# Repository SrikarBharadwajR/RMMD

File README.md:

# Project RMMD
RoboManipal Motor Driver
An Open Souce DC Brushed Motor Driver

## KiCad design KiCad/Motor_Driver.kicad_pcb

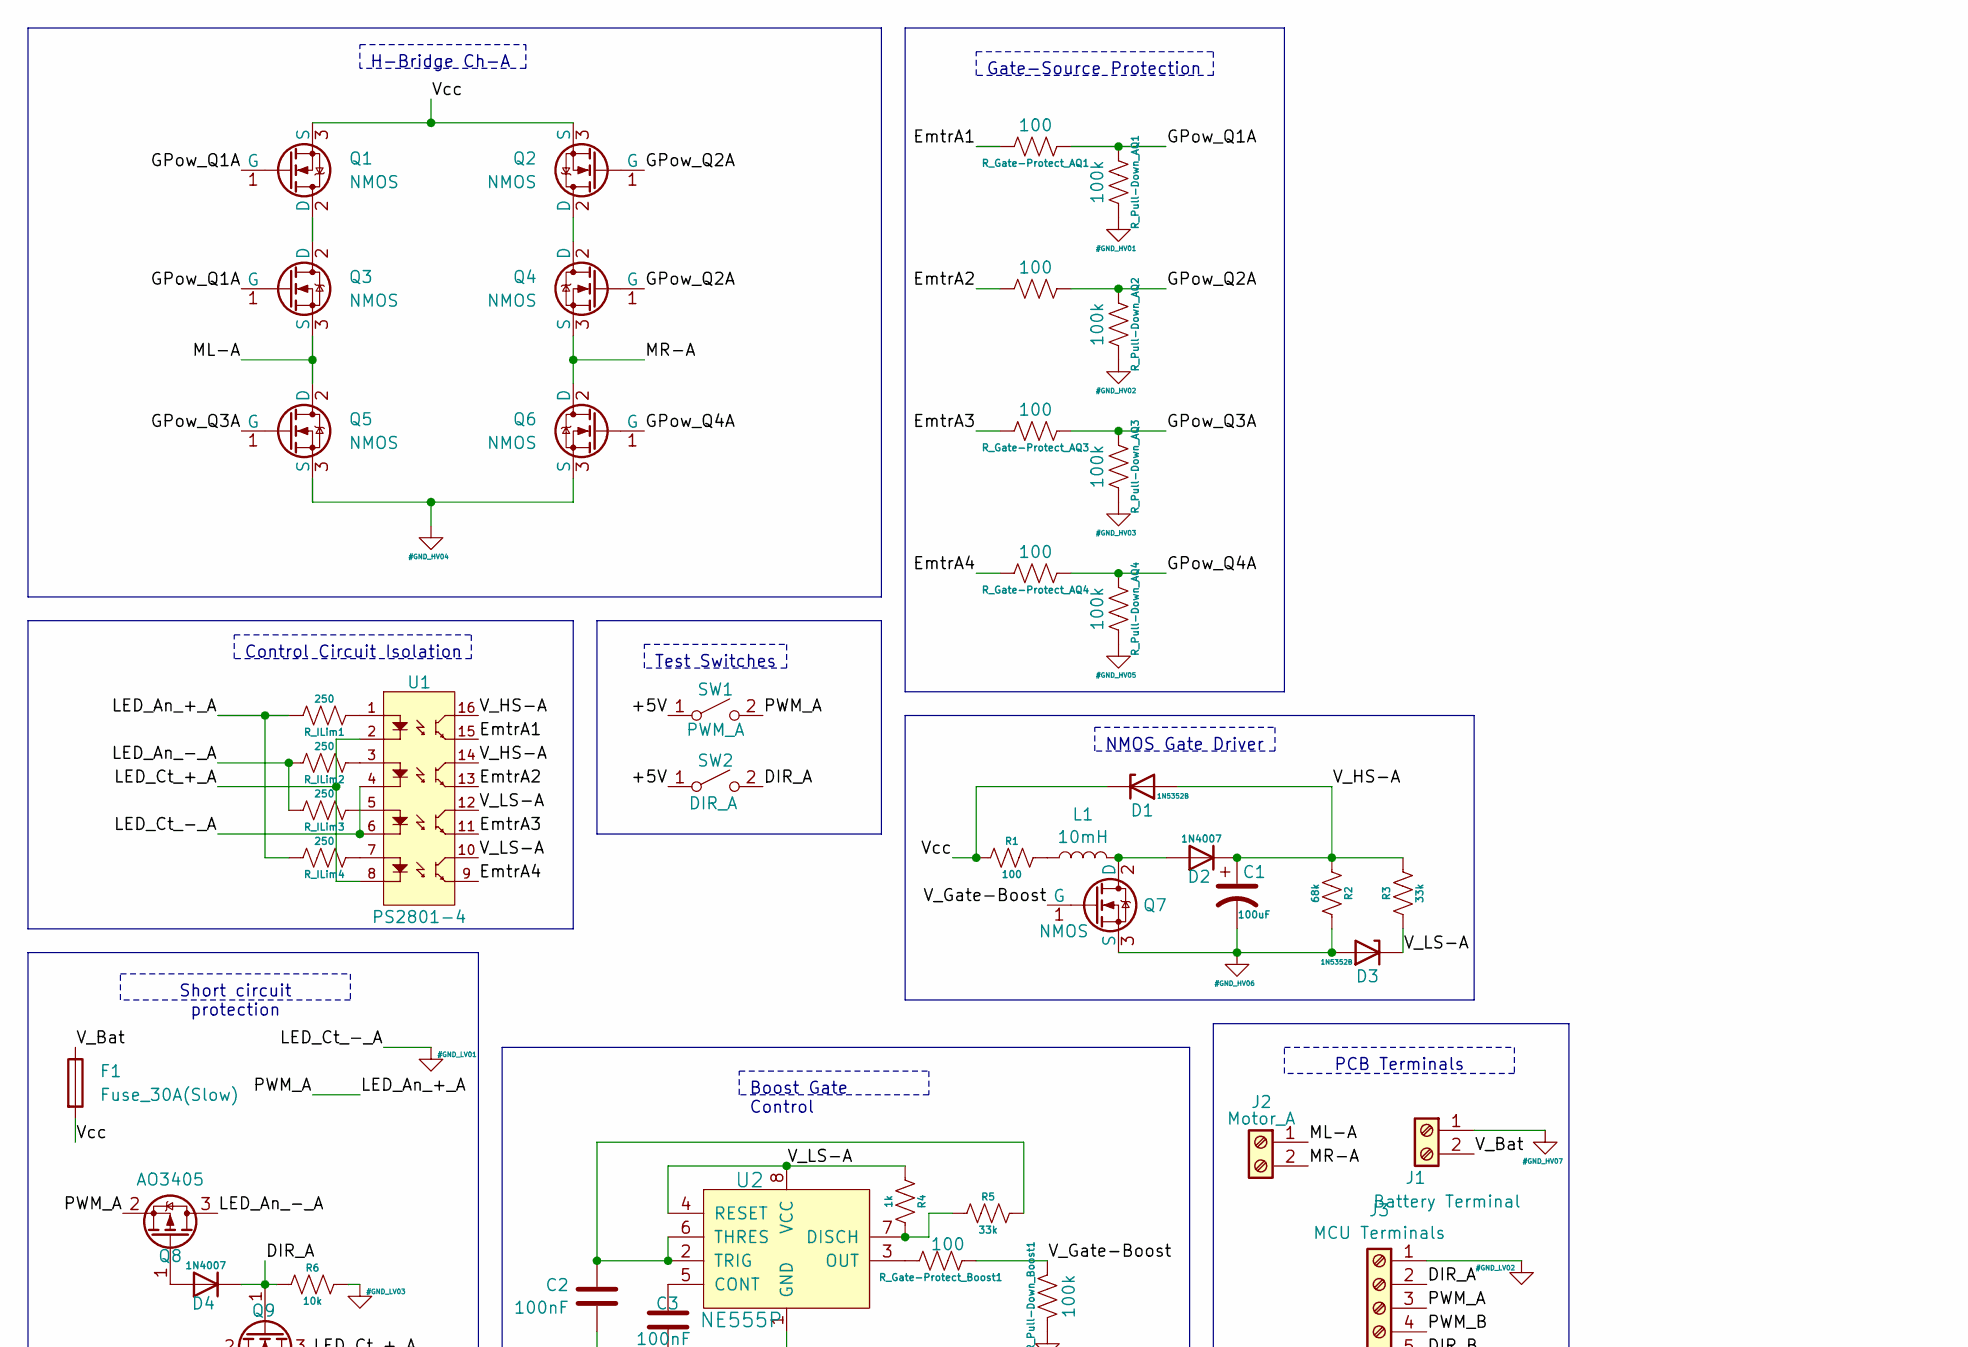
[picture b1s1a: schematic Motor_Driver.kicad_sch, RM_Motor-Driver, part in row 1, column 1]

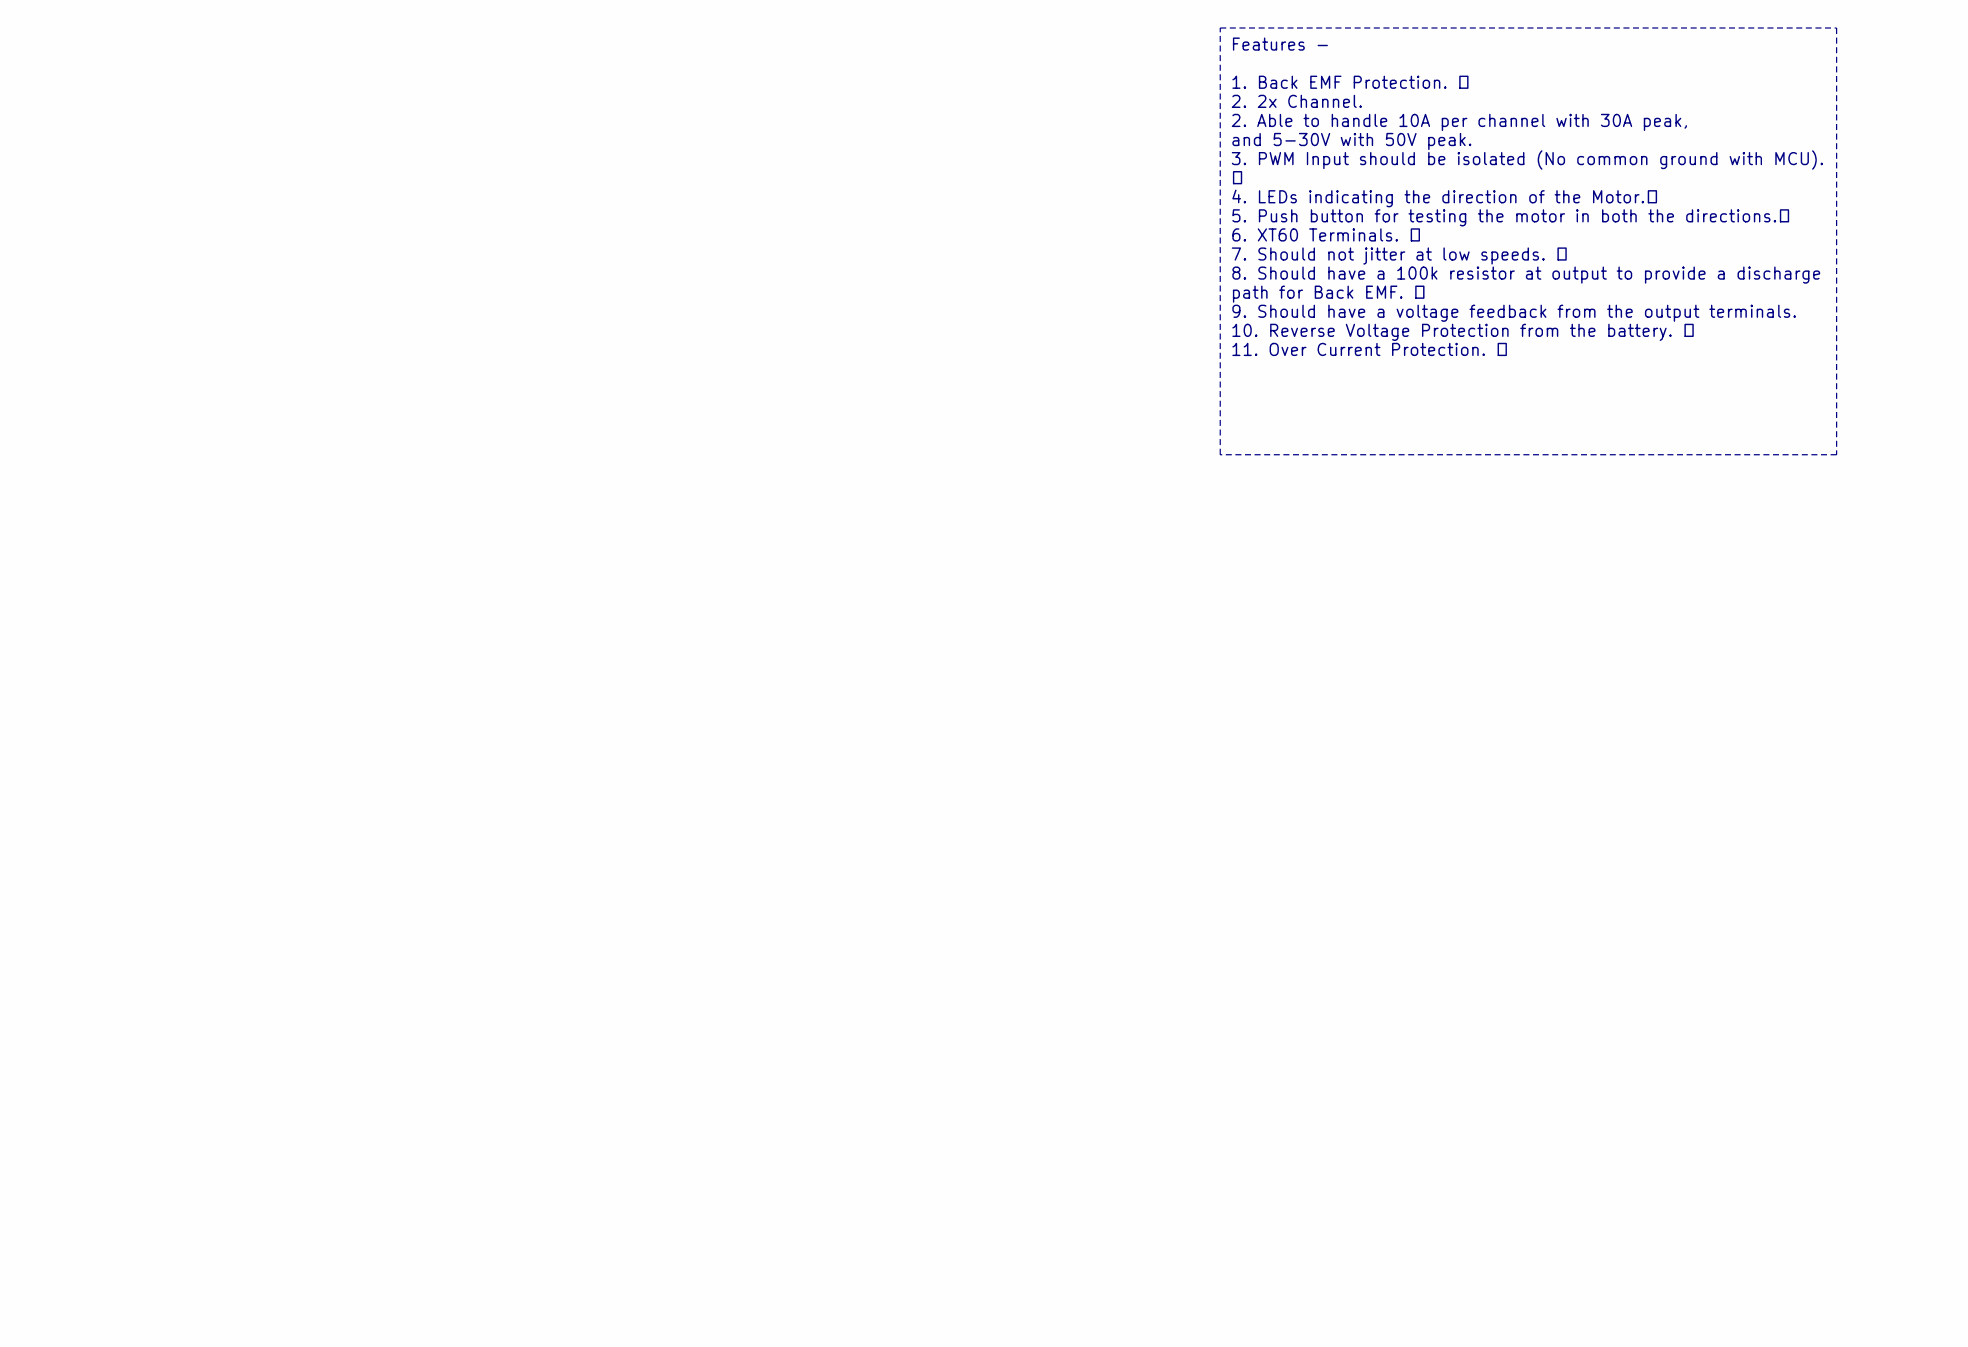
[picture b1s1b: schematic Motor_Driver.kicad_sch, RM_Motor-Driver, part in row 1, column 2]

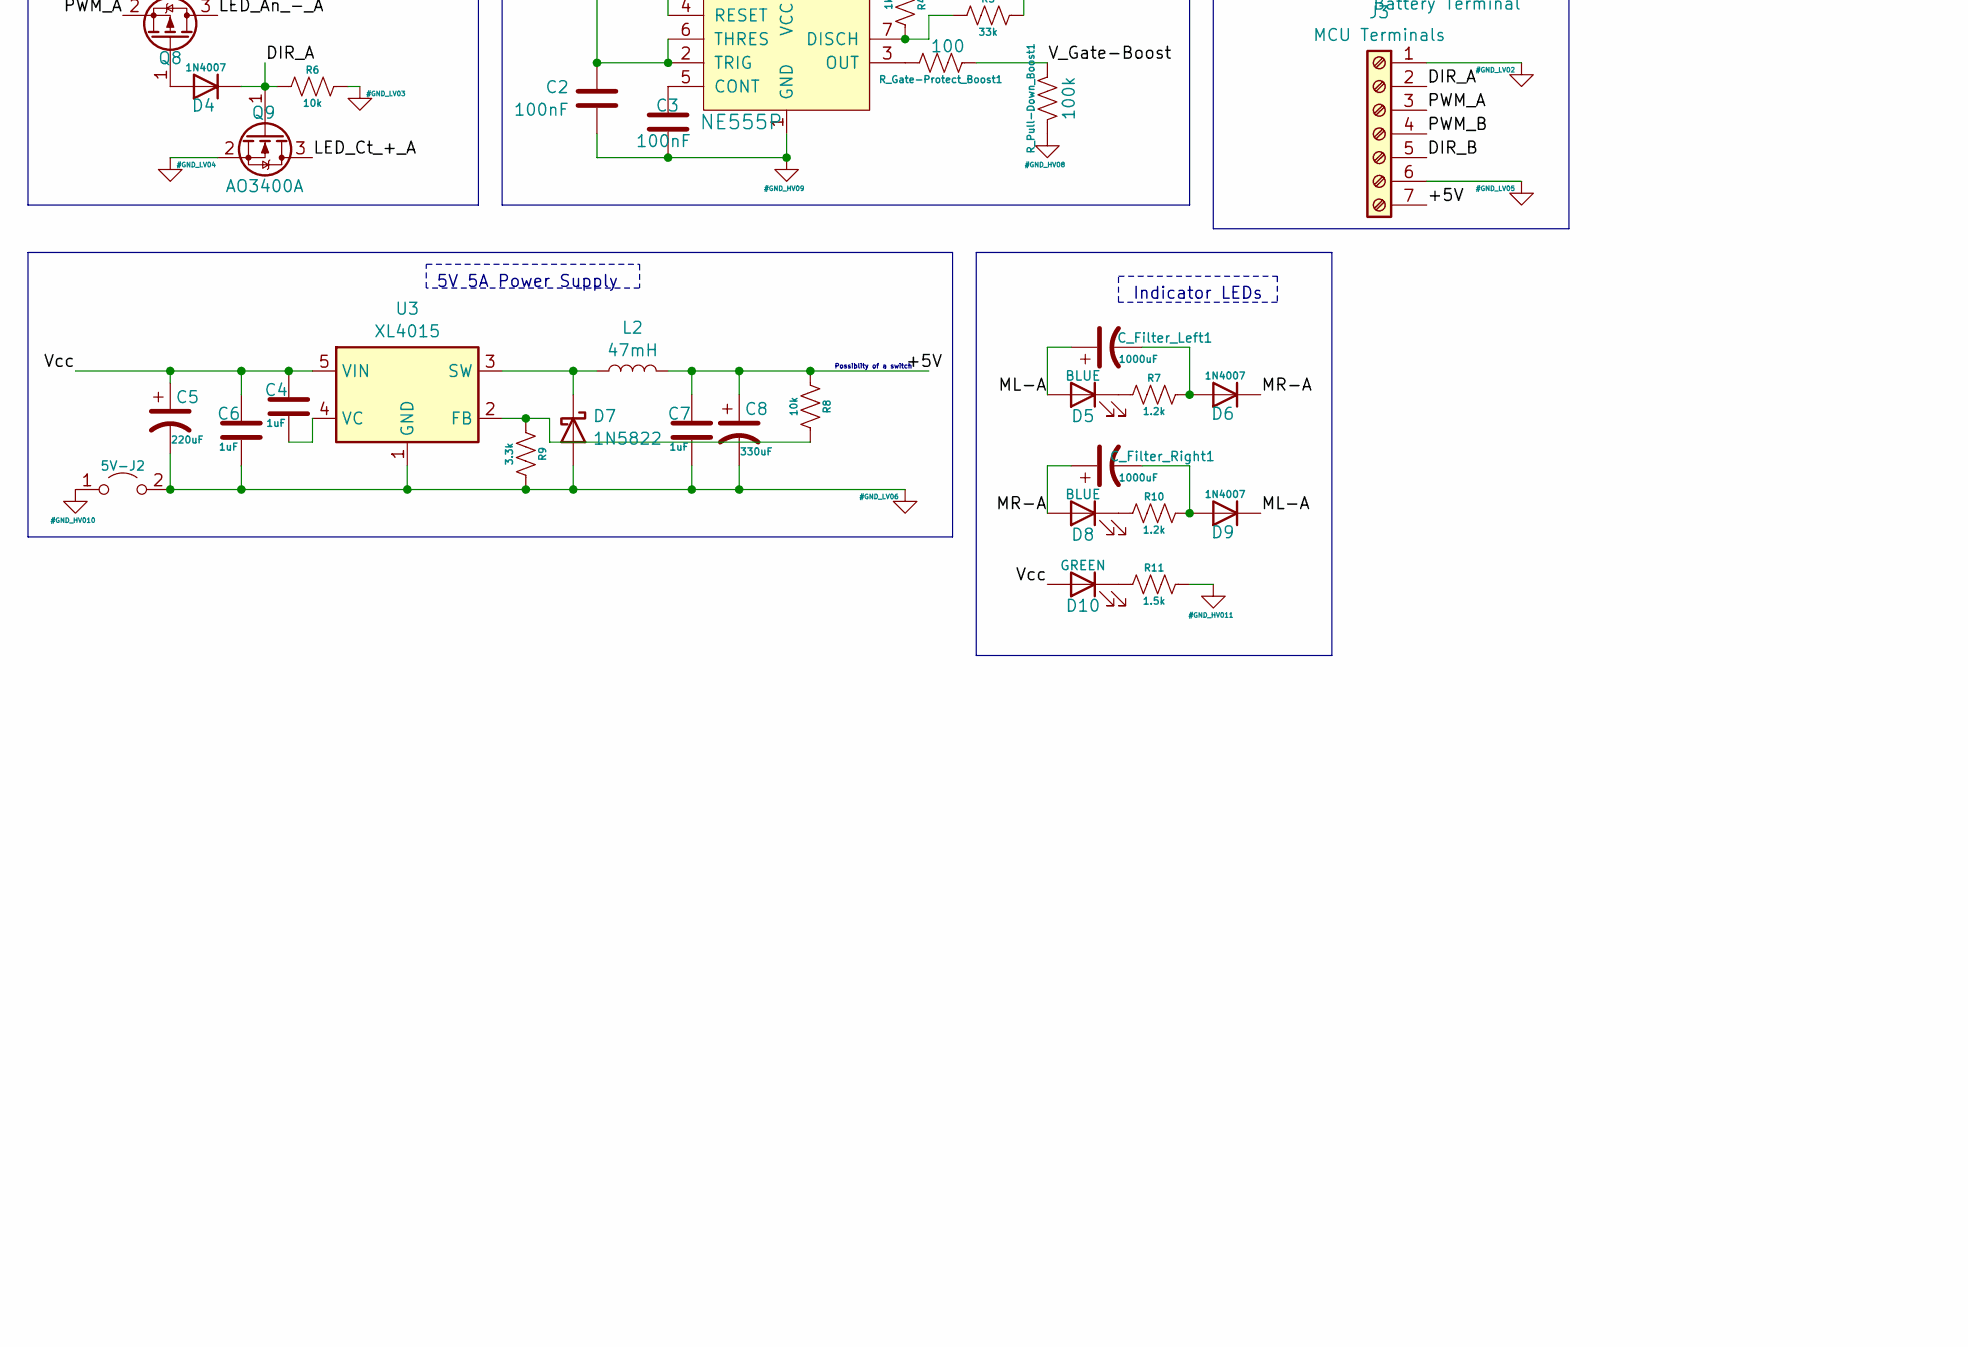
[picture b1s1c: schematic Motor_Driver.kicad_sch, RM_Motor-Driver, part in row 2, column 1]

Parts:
5V-J2: J-12V; PinHeader_1x02_P2.54mm_Vertical
C1: 100uF; CP_Radial_D5.0mm_P2.50mm
C2, C3: 100nF; C_Disc_D9.0mm_W5.0mm_P5.00mm
C4, C6, C7: 1uF; C_Disc_D9.0mm_W5.0mm_P5.00mm
C5: 220uF; CP_Radial_D5.0mm_P2.50mm
C8: 330uF; CP_Radial_D5.0mm_P2.50mm
C_Filter_Left1: 1000uF; CP_Radial_D18.0mm_P7.50mm
C_Filter_Right1: 1000uF; CP_Radial_D18.0mm_P7.50mm
D1, D3: 1N5352B; D_DO-41_SOD81_P10.16mm_Horizontal
D2, D4, D6, D9: 1N4007; D_DO-41_SOD81_P10.16mm_Horizontal
D5, D8: BLUE; LED_D3.0mm_Clear
D7: 1N5822; D_DO-201AD_P15.24mm_Horizontal
D10: GREEN; LED_D3.0mm
F1: Fuse_30A(Slow); Fuseholder_Cylinder-5x20mm_Schurter_0031_8201_Horizontal_Op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
J1: Battery Terminal; AMASS_XT60-F_1x02_P7.20mm_Vertical
J2: Motor_A; AMASS_XT60-F_1x02_P7.20mm_Vertical
J3: MCU Terminals; JST_EH_B7B-EH-A_1x07_P2.50mm_Vertical
L1: 10mH; L_Axial_L5.3mm_D2.2mm_P7.62mm_Horizontal_Vishay_IM-1
L2: 47mH; L_Toroid_Vertical_L22.4mm_W10.2mm_P7.90mm_Vishay_TJ4
Q1, Q2, Q3, Q4, Q5, Q6, Q7: NMOS; TO-220-3_Vertical
Q8: AO3405; SOT-23
Q9: AO3400A; SOT-23
R1: 100; R_Axial_DIN0204_L3.6mm_D1.6mm_P5.08mm_Horizontal
R2: 68k; R_Axial_DIN0204_L3.6mm_D1.6mm_P5.08mm_Horizontal
R3, R5: 33k; R_Axial_DIN0204_L3.6mm_D1.6mm_P5.08mm_Horizontal
R4: 1k; R_Axial_DIN0204_L3.6mm_D1.6mm_P5.08mm_Horizontal
R6, R8: 10k; R_Axial_DIN0204_L3.6mm_D1.6mm_P5.08mm_Horizontal
R7, R10: 1.2k; R_Axial_DIN0204_L3.6mm_D1.6mm_P5.08mm_Horizontal
R9: 3.3k; R_Axial_DIN0204_L3.6mm_D1.6mm_P5.08mm_Horizontal
R11: 1.5k; R_Axial_DIN0204_L3.6mm_D1.6mm_P5.08mm_Horizontal
R_Gate-Protect_AQ1, R_Gate-Protect_AQ2, R_Gate-Protect_AQ3, R_Gate-Protect_AQ4: 100; R_Axial_DIN0204_L3.6mm_D1.6mm_P5.08mm_Horizontal
R_Gate-Protect_Boost1: 100; R_Axial_DIN0204_L3.6mm_D1.6mm_P5.08mm_Horizontal
R_ILim1, R_ILim2, R_ILim3, R_ILim4: 250; R_Axial_DIN0204_L3.6mm_D1.6mm_P5.08mm_Horizontal
R_Pull-Down_AQ1, R_Pull-Down_AQ2, R_Pull-Down_AQ3, R_Pull-Down_AQ4: 100k; R_Axial_DIN0204_L3.6mm_D1.6mm_P5.08mm_Horizontal
R_Pull-Down_Boost1: 100k; R_Axial_DIN0204_L3.6mm_D1.6mm_P5.08mm_Horizontal
SW1: PWM_A; SW_PUSH_6mm_H5mm
SW2: DIR_A; SW_PUSH_6mm_H5mm
U1: PS2801-4; DIP-16_W7.62mm
U2: NE555P; DIP-8_W7.62mm; MPN NE555P; Digi-Key_PN 296-1411-5-ND
U3: XL4015; TO-263-5_TabPin3

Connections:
/+5V: C7.1, C8.1, J3.7, L2.2, R8.2, SW1.1 (A), SW2.1 (A)
/DIR_A: D4.1 (K), J3.2, Q9.1 (G), R6.2, SW2.2 (B)
/DIR_B: J3.5
/EmtrA1: R_Gate-Protect_AQ1.1, U1.15 (EM1)
/EmtrA2: R_Gate-Protect_AQ2.1, U1.13 (EM2)
/EmtrA3: R_Gate-Protect_AQ3.1, U1.11 (EM3)
/EmtrA4: R_Gate-Protect_AQ4.1, U1.9 (EM4)
/GPow_Q1A: Q1.1 (G), Q3.1 (G), R_Gate-Protect_AQ1.2, R_Pull-Down_AQ1.2
/GPow_Q2A: Q2.1 (G), Q4.1 (G), R_Gate-Protect_AQ2.2, R_Pull-Down_AQ2.2
/GPow_Q3A: Q5.1 (G), R_Gate-Protect_AQ3.2, R_Pull-Down_AQ3.2
/GPow_Q4A: Q6.1 (G), R_Gate-Protect_AQ4.2, R_Pull-Down_AQ4.2
/LED_An_+_A: J3.3, Q8.2 (S), R_ILim1.1, R_ILim4.1, SW1.2 (B)
/LED_An_-_A: Q8.3 (D), R_ILim2.1, R_ILim3.1
/LED_Ct_+_A: Q9.3 (D), U1.2 (C1), U1.8 (C4)
/ML-A: C_Filter_Left1.1, D5.2 (A), D9.1 (K), J2.1, Q3.3 (S), Q5.2 (D)
/MR-A: C_Filter_Right1.1, D6.1 (K), D8.2 (A), J2.2, Q4.3 (S), Q6.2 (D)
/PWM_B: J3.4
/V_Bat: F1.1, J1.2
/V_Gate-Boost: Q7.1 (G), R_Gate-Protect_Boost1.2, R_Pull-Down_Boost1.2
/V_HS-A: C1.1, D1.2 (A), D2.1 (K), R2.2, R3.1, U1.14 (CL2), U1.16 (CL1)
/V_LS-A: D3.1 (K), R3.2, R4.2, U1.10 (CL4), U1.12 (CL3), U2.4 (RESET), U2.8 (VCC)
/Vcc: C4.1, C5.1, C6.1, D1.1 (K), D10.2 (A), F1.2, Q1.3 (S), Q2.3 (S), R1.2, U3.5 (VIN)
GND: 5V-J2.1 (A), C1.2, C2.2, C3.2, D3.2 (A), J1.1, Q5.3 (S), Q6.3 (S), Q7.3 (S), R2.1, R11.1, R_Pull-Down_AQ1.1, R_Pull-Down_AQ2.1, R_Pull-Down_AQ3.1, R_Pull-Down_AQ4.1, R_Pull-Down_Boost1.1, U2.1 (GND)
GND2: 5V-J2.2 (B), C5.2, C6.2, C7.2, C8.2, D7.2 (A), J3.1, J3.6, Q9.2 (S), R6.1, R9.1, U1.4 (C2), U1.6 (C3), U3.1 (GND)
unnamed: D2.2 (A), L1.2, Q7.2 (D)
unnamed: D4.2 (A), Q8.1 (G)
unnamed: D5.1 (K), R7.2
unnamed: C_Filter_Left1.2, D6.2 (A), R7.1
unnamed: D7.1 (K), L2.1, U3.3 (SW)
unnamed: D8.1 (K), R10.2
unnamed: C_Filter_Right1.2, D9.2 (A), R10.1
unnamed: D10.1 (K), R11.2
unnamed: L1.1, R1.1
unnamed: Q1.2 (D), Q3.2 (D)
unnamed: Q2.2 (D), Q4.2 (D)
unnamed: R_ILim1.2, U1.1 (A1)
unnamed: R_ILim2.2, U1.3 (A2)
unnamed: R_ILim3.2, U1.5 (A3)
unnamed: R_ILim4.2, U1.7 (A4)
unnamed: C3.1, U2.5 (CONT)
unnamed: R4.1, R5.2, U2.7 (DISCH)
unnamed: R_Gate-Protect_Boost1.1, U2.3 (OUT)
unnamed: C2.1, R5.1, U2.2 (TRIG), U2.6 (THRES)
unnamed: R8.1, R9.2, U3.2 (FB)
unnamed: C4.2, U3.4 (VC)

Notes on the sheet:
NMOS Gate Driver
Notes: 1. Driving frequency shouldn't increase more than 100kHz and should not be less than 1kHz.
Features - 1. Back EMF Protection. ✓ 2. 2x Channel. 2. Able to handle 10A per channel with 30A peak, and 5-30V with 50V peak. 3. PWM Input should be isolated (No common ground with MCU). ✓ 4. LEDs indicating the direction of the Motor.✓ 5. Push button for testing the motor in both the directions.✓ 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
PCB Terminals
5V 5A Power Supply
Control Circuit Isolation
Boost Gate Control
Gate-Source Protection
Short circuit protection
Indicator LEDs
Test Switches
H-Bridge Ch-A
Possiblity of a switch

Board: 2 copper layers, 66 parts (2 on the bottom side), 43 nets, no tracks yet.

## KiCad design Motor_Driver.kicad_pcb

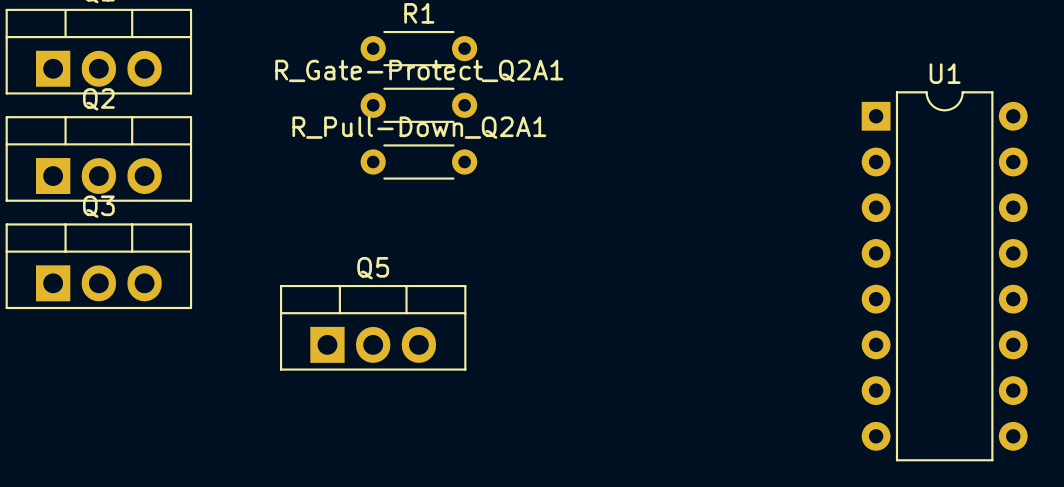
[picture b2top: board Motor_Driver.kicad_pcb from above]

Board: 2 copper layers, 8 parts (0 on the bottom side), 6 nets, no tracks yet.

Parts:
Q1, Q2, Q3, Q5: NMOS; TO-220-3_Vertical
R1: R_PD; R_Axial_DIN0204_L3.6mm_D1.6mm_P5.08mm_Horizontal
R_Gate-Protect_Q2A1: 10; R_Axial_DIN0204_L3.6mm_D1.6mm_P5.08mm_Horizontal
R_Pull-Down_Q2A1: 22k; R_Axial_DIN0204_L3.6mm_D1.6mm_P5.08mm_Horizontal
U1: PS2801-4; DIP-16_W7.62mm

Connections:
/ML-A: Q1.2 (D), Q5.3 (S)
/MR-A: Q2.3 (S), Q3.2 (D)
/Vcc: Q2.2 (D), Q5.2 (D)
GND: Q1.3 (S), Q3.3 (S), R1.2, R_Pull-Down_Q2A1.2
unnamed: Q5.1 (G), R1.1
unnamed: R_Gate-Protect_Q2A1.2, R_Pull-Down_Q2A1.1

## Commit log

2023-07-11 Refresh
2023-07-15 Low Side Driver
2023-07-15 5v5A supply
2023-07-17 Short Circuit Protection
2023-07-25 Added NMOS Gate Drivers
2023-07-25 Schematic PDF update
